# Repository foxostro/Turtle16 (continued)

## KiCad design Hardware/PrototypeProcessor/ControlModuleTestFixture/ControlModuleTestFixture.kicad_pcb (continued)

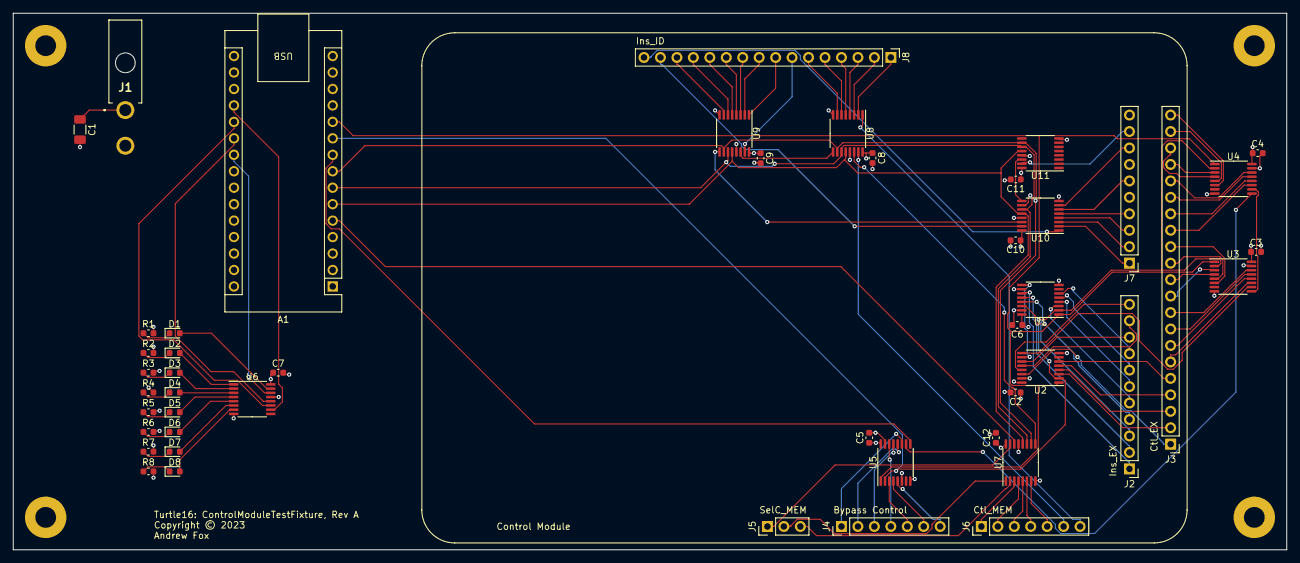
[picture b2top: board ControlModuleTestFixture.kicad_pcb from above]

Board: 4 copper layers, 196.5 x 82.8 mm, 52 parts (0 on the bottom side), 109 nets.

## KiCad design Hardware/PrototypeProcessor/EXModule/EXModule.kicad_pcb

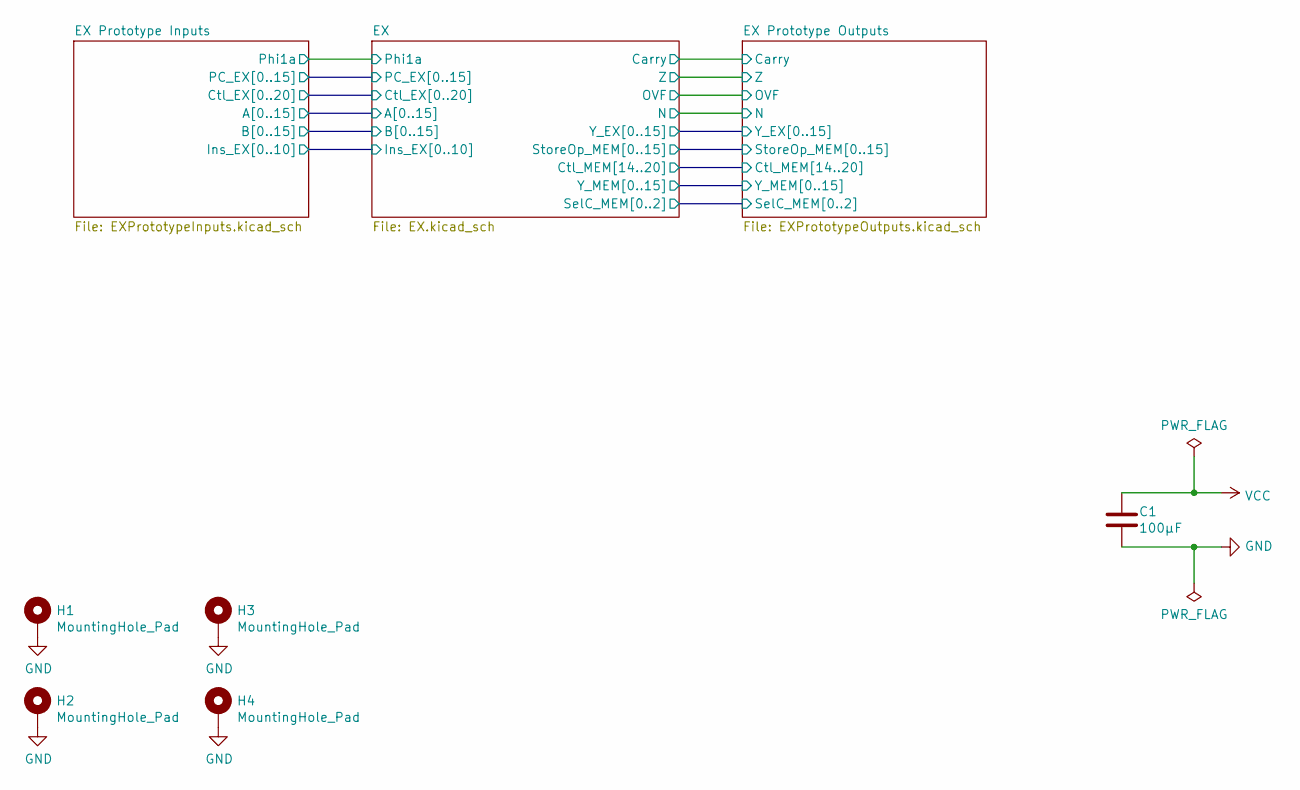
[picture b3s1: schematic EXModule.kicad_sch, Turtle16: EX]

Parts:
C1: 100µF; C_1206_3216Metric_Pad1.33x1.80mm_HandSolder
H1, H2, H3, H4: MountingHole_Pad; MountingHole_3.2mm_M3_Pad

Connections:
GND: C1.2, H1.1, H2.1, H3.1, H4.1; also elsewhere on the board
VCC: C1.1; also elsewhere on the board

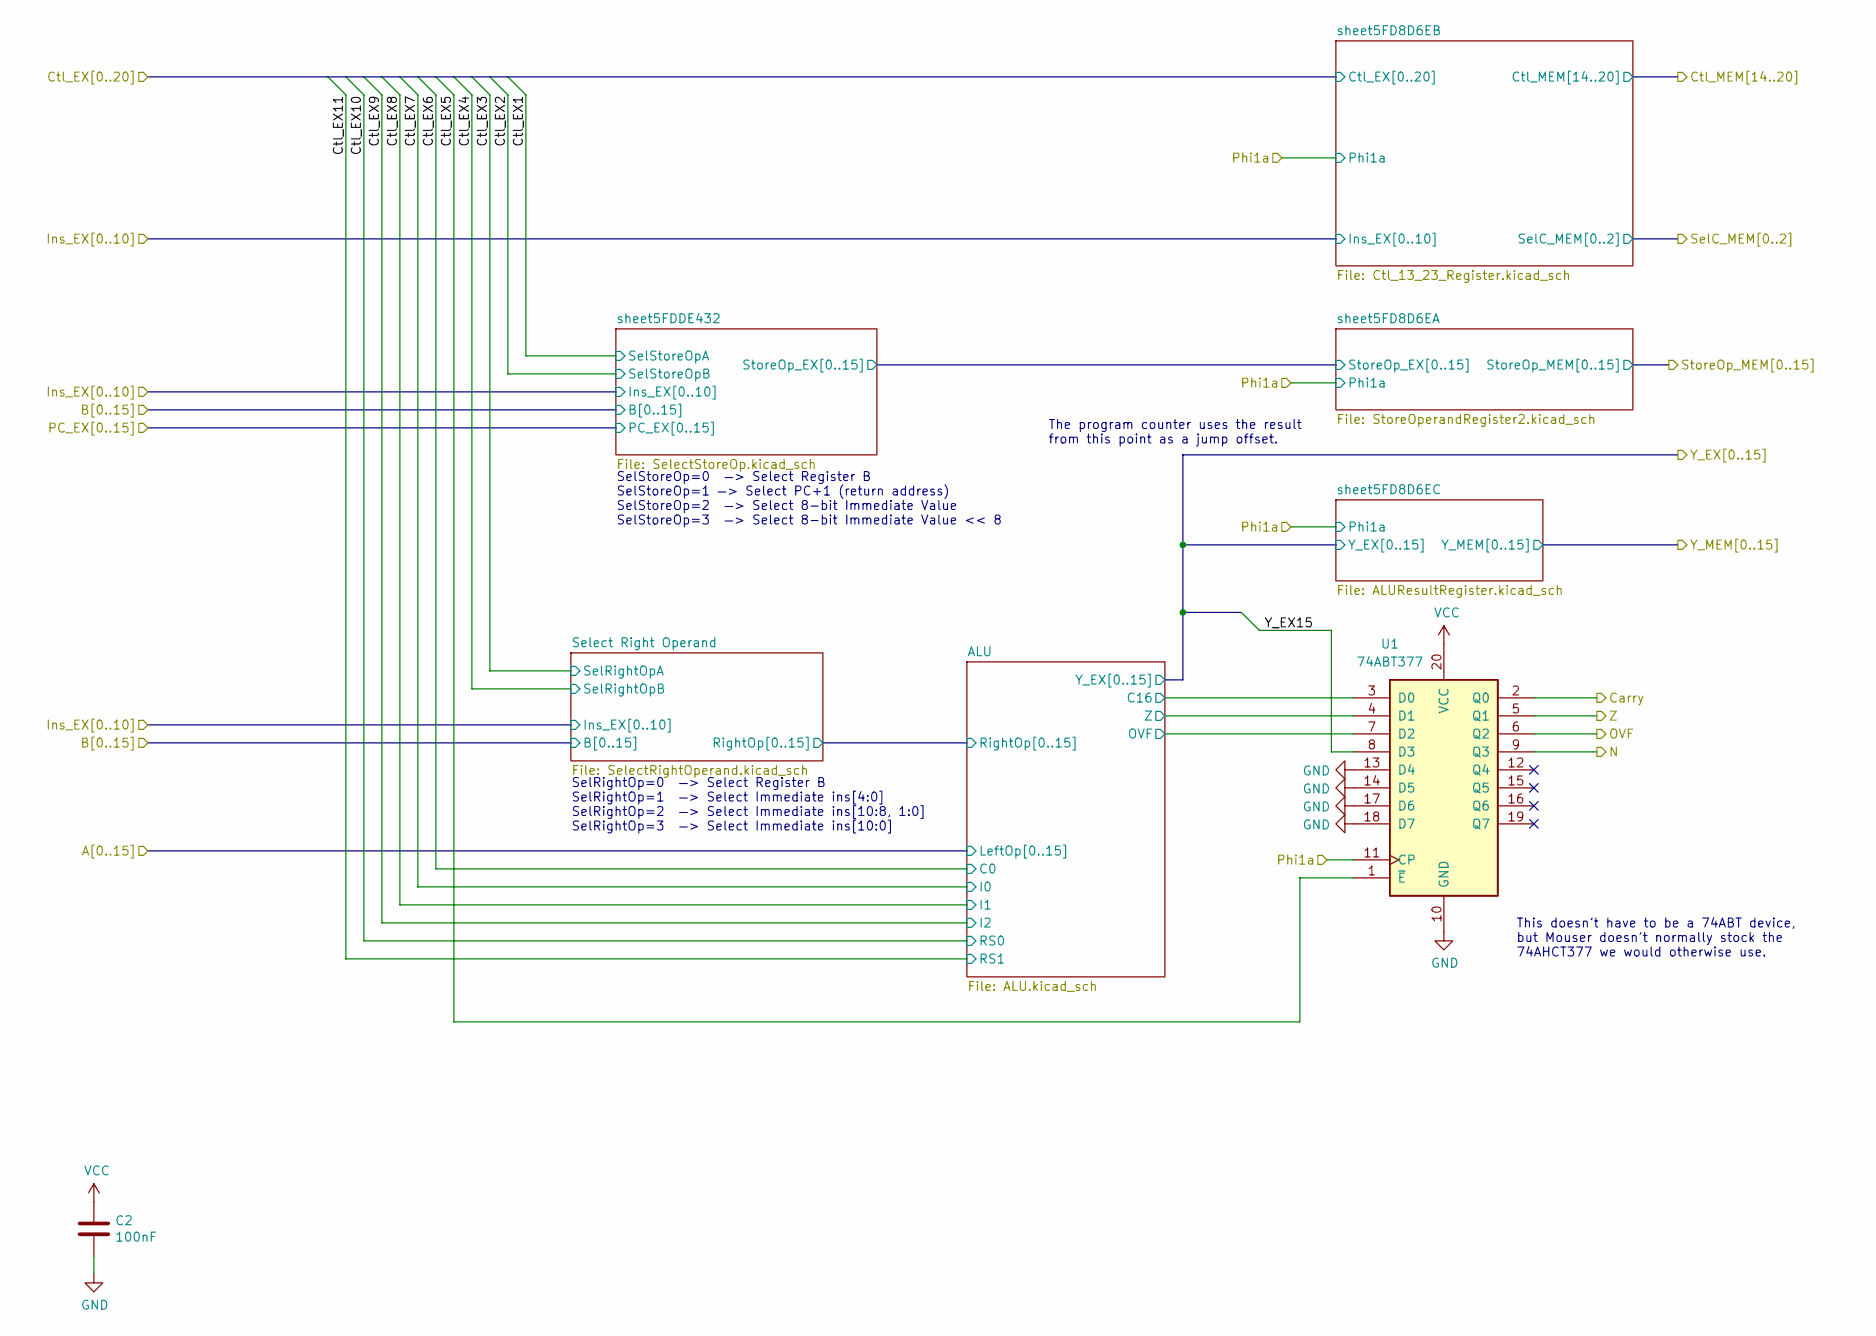
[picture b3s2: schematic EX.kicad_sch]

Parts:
C2: 100nF; C_0603_1608Metric_Pad1.08x0.95mm_HandSolder
U1: 74ABT377; TSSOP-20_4.4x6.5mm_P0.65mm

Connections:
/EX Prototype Inputs/Ctl_EX5: U1.1 (~E); also elsewhere on the board
/EX Prototype Inputs/Phi1a: U1.11 (CP); also elsewhere on the board
/EX Prototype Outputs/Carry: U1.2 (Q0); also elsewhere on the board
/EX Prototype Outputs/N: U1.9 (Q3); also elsewhere on the board
/EX Prototype Outputs/OVF: U1.6 (Q2); also elsewhere on the board
/EX Prototype Outputs/Y_EX15: U1.8 (D3); also elsewhere on the board
/EX Prototype Outputs/Z: U1.5 (Q1); also elsewhere on the board
/EX/ALU/C16: U1.3 (D0); also elsewhere on the board
/EX/ALU/OVF: U1.7 (D2); also elsewhere on the board
/EX/ALU/Z: U1.4 (D1); also elsewhere on the board
GND: C2.2, U1.10 (GND), U1.13 (D4), U1.14 (D5), U1.17 (D6), U1.18 (D7); also elsewhere on the board
VCC: C2.1, U1.20 (VCC); also elsewhere on the board

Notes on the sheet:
SelStoreOp=0 —> Select Register B SelStoreOp=1 —> Select PC+1 (return address) SelStoreOp=2 —> Select 8-bit Immediate Value SelStoreOp=3 —> Select 8-bit Immediate Value << 8
This doesn’t have to be a 74ABT device, but Mouser doesn’t normally stock the 74AHCT377 we would otherwise use.
SelRightOp=0 —> Select Register B SelRightOp=1 —> Select Immediate ins[4:0] SelRightOp=2 —> Select Immediate ins[10:8, 1:0] SelRightOp=3 —> Select Immediate ins[10:0]
The program counter uses the result from this point as a jump offset.

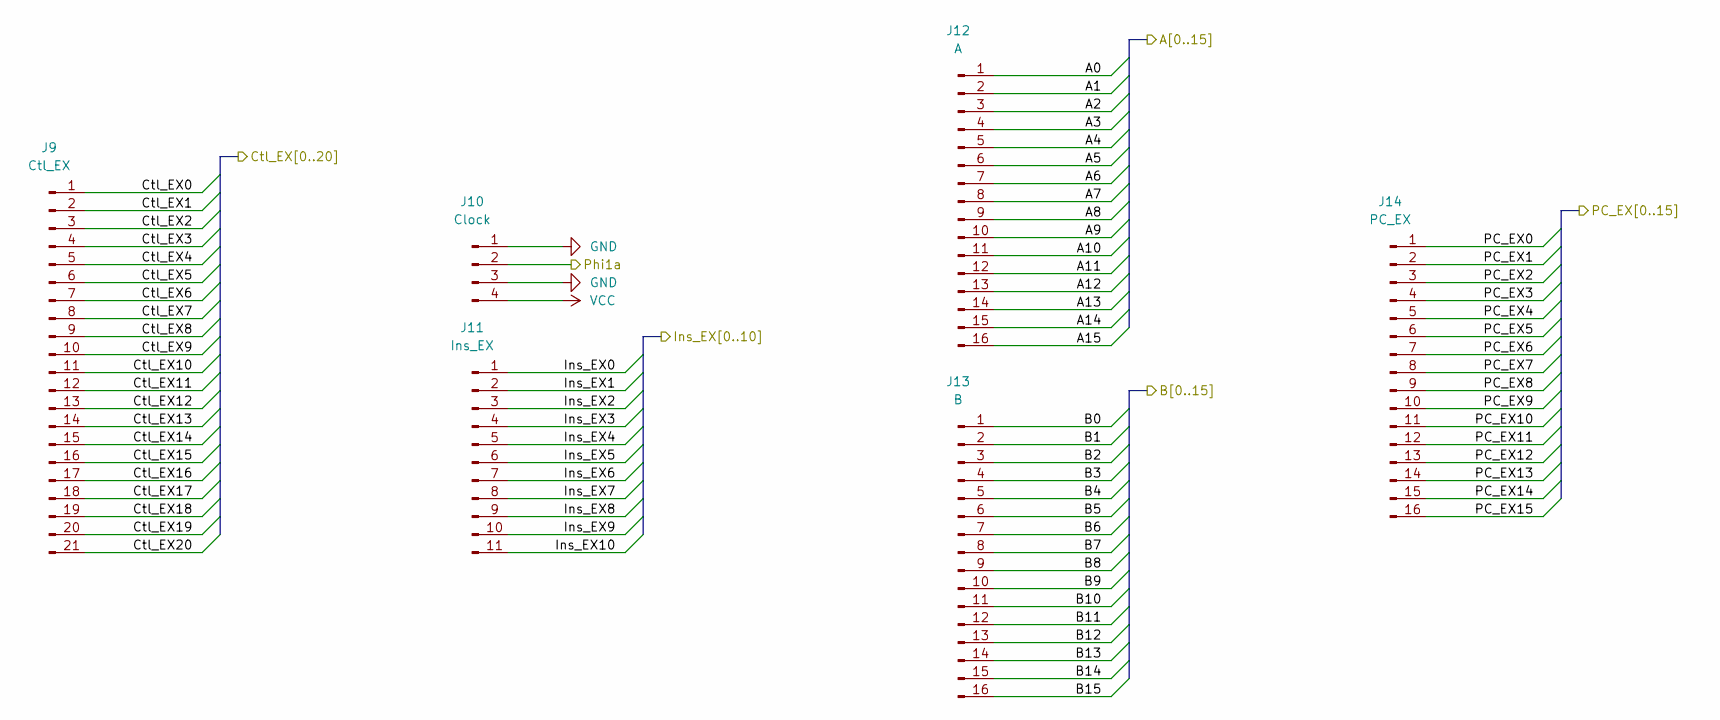
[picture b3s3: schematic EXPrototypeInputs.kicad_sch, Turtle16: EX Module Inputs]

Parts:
J9: Ctl_EX; PinHeader_1x21_P2.54mm_Vertical
J10: Clock; PinHeader_1x04_P2.54mm_Vertical
J11: Ins_EX; PinHeader_1x11_P2.54mm_Vertical
J12: A; PinHeader_1x16_P2.54mm_Vertical
J13: B; PinHeader_1x16_P2.54mm_Vertical
J14: PC_EX; PinHeader_1x16_P2.54mm_Vertical

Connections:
/EX Prototype Inputs/A0: J12.1; also elsewhere on the board
/EX Prototype Inputs/A1: J12.2; also elsewhere on the board
/EX Prototype Inputs/A2: J12.3; also elsewhere on the board
/EX Prototype Inputs/A3: J12.4; also elsewhere on the board
/EX Prototype Inputs/A4: J12.5; also elsewhere on the board
/EX Prototype Inputs/A5: J12.6; also elsewhere on the board
/EX Prototype Inputs/A6: J12.7; also elsewhere on the board
/EX Prototype Inputs/A7: J12.8; also elsewhere on the board
/EX Prototype Inputs/A8: J12.9; also elsewhere on the board
/EX Prototype Inputs/A9: J12.10; also elsewhere on the board
/EX Prototype Inputs/A10: J12.11; also elsewhere on the board
/EX Prototype Inputs/A11: J12.12; also elsewhere on the board
/EX Prototype Inputs/A12: J12.13; also elsewhere on the board
/EX Prototype Inputs/A13: J12.14; also elsewhere on the board
/EX Prototype Inputs/A14: J12.15; also elsewhere on the board
/EX Prototype Inputs/A15: J12.16; also elsewhere on the board
/EX Prototype Inputs/B0: J13.1; also elsewhere on the board
/EX Prototype Inputs/B1: J13.2; also elsewhere on the board
/EX Prototype Inputs/B2: J13.3; also elsewhere on the board
/EX Prototype Inputs/B3: J13.4; also elsewhere on the board
/EX Prototype Inputs/B4: J13.5; also elsewhere on the board
/EX Prototype Inputs/B5: J13.6; also elsewhere on the board
/EX Prototype Inputs/B6: J13.7; also elsewhere on the board
/EX Prototype Inputs/B7: J13.8; also elsewhere on the board
/EX Prototype Inputs/B8: J13.9; also elsewhere on the board
/EX Prototype Inputs/B9: J13.10; also elsewhere on the board
/EX Prototype Inputs/B10: J13.11; also elsewhere on the board
/EX Prototype Inputs/B11: J13.12; also elsewhere on the board
/EX Prototype Inputs/B12: J13.13; also elsewhere on the board
/EX Prototype Inputs/B13: J13.14; also elsewhere on the board
/EX Prototype Inputs/B14: J13.15; also elsewhere on the board
/EX Prototype Inputs/B15: J13.16; also elsewhere on the board
/EX Prototype Inputs/Ctl_EX0: J9.1
/EX Prototype Inputs/Ctl_EX1: J9.2; also elsewhere on the board
/EX Prototype Inputs/Ctl_EX2: J9.3; also elsewhere on the board
/EX Prototype Inputs/Ctl_EX3: J9.4; also elsewhere on the board
/EX Prototype Inputs/Ctl_EX4: J9.5; also elsewhere on the board
/EX Prototype Inputs/Ctl_EX5: J9.6; also elsewhere on the board
/EX Prototype Inputs/Ctl_EX6: J9.7; also elsewhere on the board
/EX Prototype Inputs/Ctl_EX7: J9.8; also elsewhere on the board
/EX Prototype Inputs/Ctl_EX8: J9.9; also elsewhere on the board
/EX Prototype Inputs/Ctl_EX9: J9.10; also elsewhere on the board
/EX Prototype Inputs/Ctl_EX10: J9.11; also elsewhere on the board
/EX Prototype Inputs/Ctl_EX11: J9.12; also elsewhere on the board
/EX Prototype Inputs/Ctl_EX12: J9.13
/EX Prototype Inputs/Ctl_EX13: J9.14
/EX Prototype Inputs/Ctl_EX14: J9.15; also elsewhere on the board
/EX Prototype Inputs/Ctl_EX15: J9.16; also elsewhere on the board
/EX Prototype Inputs/Ctl_EX16: J9.17; also elsewhere on the board
/EX Prototype Inputs/Ctl_EX17: J9.18; also elsewhere on the board
/EX Prototype Inputs/Ctl_EX18: J9.19; also elsewhere on the board
/EX Prototype Inputs/Ctl_EX19: J9.20; also elsewhere on the board
/EX Prototype Inputs/Ctl_EX20: J9.21; also elsewhere on the board
/EX Prototype Inputs/Ins_EX0: J11.1; also elsewhere on the board
/EX Prototype Inputs/Ins_EX1: J11.2; also elsewhere on the board
/EX Prototype Inputs/Ins_EX2: J11.3; also elsewhere on the board
/EX Prototype Inputs/Ins_EX3: J11.4; also elsewhere on the board
/EX Prototype Inputs/Ins_EX4: J11.5; also elsewhere on the board
/EX Prototype Inputs/Ins_EX5: J11.6; also elsewhere on the board
/EX Prototype Inputs/Ins_EX6: J11.7; also elsewhere on the board
/EX Prototype Inputs/Ins_EX7: J11.8; also elsewhere on the board
/EX Prototype Inputs/Ins_EX8: J11.9; also elsewhere on the board
/EX Prototype Inputs/Ins_EX9: J11.10; also elsewhere on the board
/EX Prototype Inputs/Ins_EX10: J11.11; also elsewhere on the board
/EX Prototype Inputs/PC_EX0: J14.1; also elsewhere on the board
/EX Prototype Inputs/PC_EX1: J14.2; also elsewhere on the board
/EX Prototype Inputs/PC_EX2: J14.3; also elsewhere on the board
/EX Prototype Inputs/PC_EX3: J14.4; also elsewhere on the board
/EX Prototype Inputs/PC_EX4: J14.5; also elsewhere on the board
/EX Prototype Inputs/PC_EX5: J14.6; also elsewhere on the board
/EX Prototype Inputs/PC_EX6: J14.7; also elsewhere on the board
/EX Prototype Inputs/PC_EX7: J14.8; also elsewhere on the board
/EX Prototype Inputs/PC_EX8: J14.9; also elsewhere on the board
/EX Prototype Inputs/PC_EX9: J14.10; also elsewhere on the board
/EX Prototype Inputs/PC_EX10: J14.11; also elsewhere on the board
/EX Prototype Inputs/PC_EX11: J14.12; also elsewhere on the board
/EX Prototype Inputs/PC_EX12: J14.13; also elsewhere on the board
/EX Prototype Inputs/PC_EX13: J14.14; also elsewhere on the board
/EX Prototype Inputs/PC_EX14: J14.15; also elsewhere on the board
/EX Prototype Inputs/PC_EX15: J14.16; also elsewhere on the board
/EX Prototype Inputs/Phi1a: J10.2; also elsewhere on the board
GND: J10.1, J10.3; also elsewhere on the board
VCC: J10.4; also elsewhere on the board

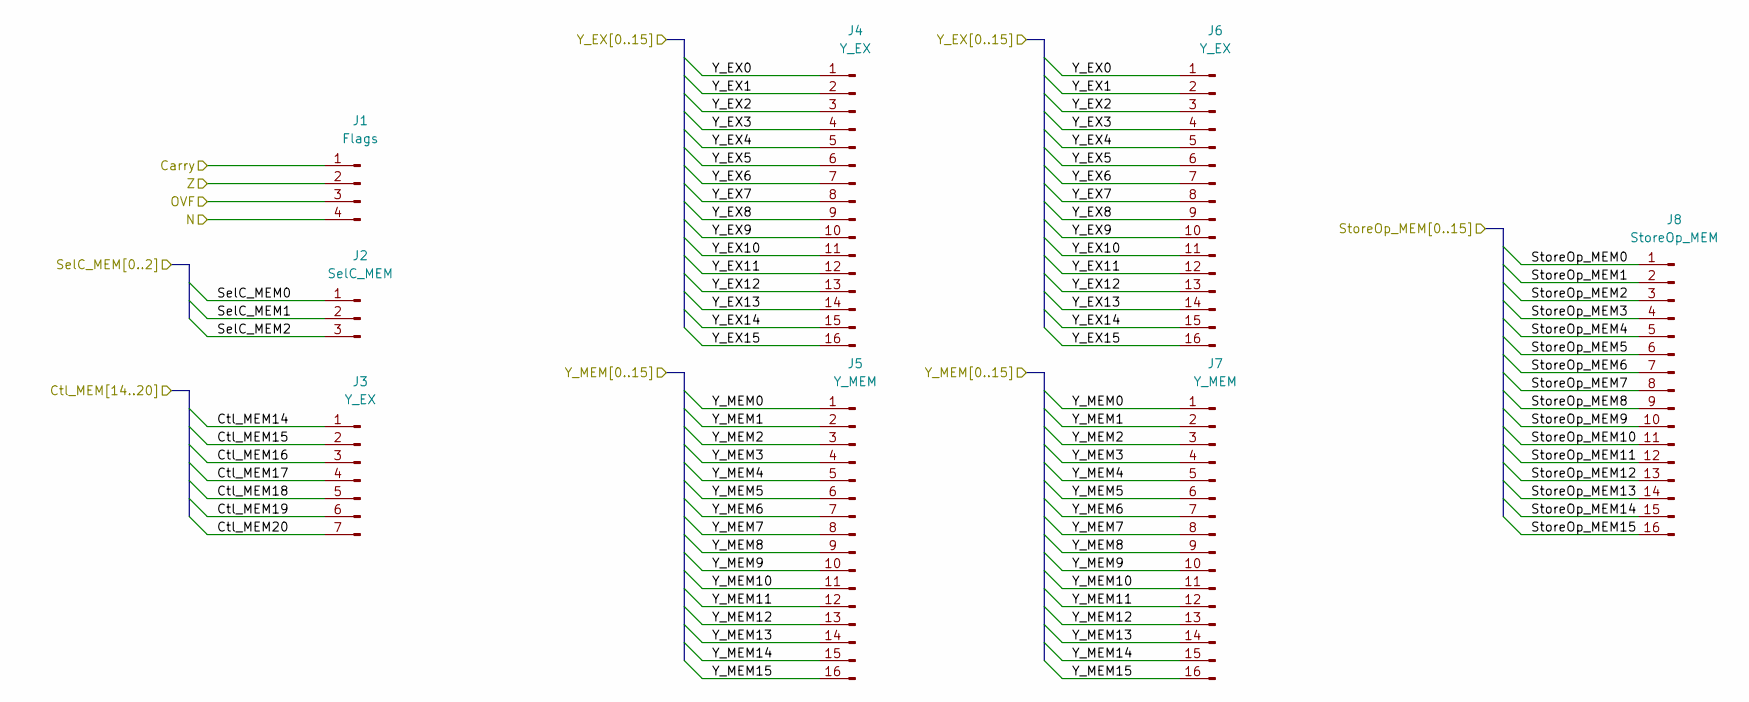
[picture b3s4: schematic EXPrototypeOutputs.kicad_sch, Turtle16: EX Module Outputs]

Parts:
J1: Flags; PinHeader_1x04_P2.54mm_Vertical
J2: SelC_MEM; PinHeader_1x03_P2.54mm_Vertical
J3: Y_EX; PinHeader_1x07_P2.54mm_Vertical
J4, J6: Y_EX; PinHeader_1x16_P2.54mm_Vertical
J5, J7: Y_MEM; PinHeader_1x16_P2.54mm_Vertical
J8: StoreOp_MEM; PinHeader_1x16_P2.54mm_Vertical

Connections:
/EX Prototype Outputs/Carry: J1.1; also elsewhere on the board
/EX Prototype Outputs/Ctl_MEM14: J3.1; also elsewhere on the board
/EX Prototype Outputs/Ctl_MEM15: J3.2; also elsewhere on the board
/EX Prototype Outputs/Ctl_MEM16: J3.3; also elsewhere on the board
/EX Prototype Outputs/Ctl_MEM17: J3.4; also elsewhere on the board
/EX Prototype Outputs/Ctl_MEM18: J3.5; also elsewhere on the board
/EX Prototype Outputs/Ctl_MEM19: J3.6; also elsewhere on the board
/EX Prototype Outputs/Ctl_MEM20: J3.7; also elsewhere on the board
/EX Prototype Outputs/N: J1.4; also elsewhere on the board
/EX Prototype Outputs/OVF: J1.3; also elsewhere on the board
/EX Prototype Outputs/SelC_MEM0: J2.1; also elsewhere on the board
/EX Prototype Outputs/SelC_MEM1: J2.2; also elsewhere on the board
/EX Prototype Outputs/SelC_MEM2: J2.3; also elsewhere on the board
/EX Prototype Outputs/StoreOp_MEM0: J8.1; also elsewhere on the board
/EX Prototype Outputs/StoreOp_MEM1: J8.2; also elsewhere on the board
/EX Prototype Outputs/StoreOp_MEM2: J8.3; also elsewhere on the board
/EX Prototype Outputs/StoreOp_MEM3: J8.4; also elsewhere on the board
/EX Prototype Outputs/StoreOp_MEM4: J8.5; also elsewhere on the board
/EX Prototype Outputs/StoreOp_MEM5: J8.6; also elsewhere on the board
/EX Prototype Outputs/StoreOp_MEM6: J8.7; also elsewhere on the board
/EX Prototype Outputs/StoreOp_MEM7: J8.8; also elsewhere on the board
/EX Prototype Outputs/StoreOp_MEM8: J8.9; also elsewhere on the board
/EX Prototype Outputs/StoreOp_MEM9: J8.10; also elsewhere on the board
/EX Prototype Outputs/StoreOp_MEM10: J8.11; also elsewhere on the board
/EX Prototype Outputs/StoreOp_MEM11: J8.12; also elsewhere on the board
/EX Prototype Outputs/StoreOp_MEM12: J8.13; also elsewhere on the board
/EX Prototype Outputs/StoreOp_MEM13: J8.14; also elsewhere on the board
/EX Prototype Outputs/StoreOp_MEM14: J8.15; also elsewhere on the board
/EX Prototype Outputs/StoreOp_MEM15: J8.16; also elsewhere on the board
/EX Prototype Outputs/Y_EX0: J4.1, J6.1; also elsewhere on the board
/EX Prototype Outputs/Y_EX1: J4.2, J6.2; also elsewhere on the board
/EX Prototype Outputs/Y_EX2: J4.3, J6.3; also elsewhere on the board
/EX Prototype Outputs/Y_EX3: J4.4, J6.4; also elsewhere on the board
/EX Prototype Outputs/Y_EX4: J4.5, J6.5; also elsewhere on the board
/EX Prototype Outputs/Y_EX5: J4.6, J6.6; also elsewhere on the board
/EX Prototype Outputs/Y_EX6: J4.7, J6.7; also elsewhere on the board
/EX Prototype Outputs/Y_EX7: J4.8, J6.8; also elsewhere on the board
/EX Prototype Outputs/Y_EX8: J4.9, J6.9; also elsewhere on the board
/EX Prototype Outputs/Y_EX9: J4.10, J6.10; also elsewhere on the board
/EX Prototype Outputs/Y_EX10: J4.11, J6.11; also elsewhere on the board
/EX Prototype Outputs/Y_EX11: J4.12, J6.12; also elsewhere on the board
/EX Prototype Outputs/Y_EX12: J4.13, J6.13; also elsewhere on the board
/EX Prototype Outputs/Y_EX13: J4.14, J6.14; also elsewhere on the board
/EX Prototype Outputs/Y_EX14: J4.15, J6.15; also elsewhere on the board
/EX Prototype Outputs/Y_EX15: J4.16, J6.16; also elsewhere on the board
/EX Prototype Outputs/Y_MEM0: J5.1, J7.1; also elsewhere on the board
/EX Prototype Outputs/Y_MEM1: J5.2, J7.2; also elsewhere on the board
/EX Prototype Outputs/Y_MEM2: J5.3, J7.3; also elsewhere on the board
/EX Prototype Outputs/Y_MEM3: J5.4, J7.4; also elsewhere on the board
/EX Prototype Outputs/Y_MEM4: J5.5, J7.5; also elsewhere on the board
/EX Prototype Outputs/Y_MEM5: J5.6, J7.6; also elsewhere on the board
/EX Prototype Outputs/Y_MEM6: J5.7, J7.7; also elsewhere on the board
/EX Prototype Outputs/Y_MEM7: J5.8, J7.8; also elsewhere on the board
/EX Prototype Outputs/Y_MEM8: J5.9, J7.9; also elsewhere on the board
/EX Prototype Outputs/Y_MEM9: J5.10, J7.10; also elsewhere on the board
/EX Prototype Outputs/Y_MEM10: J5.11, J7.11; also elsewhere on the board
/EX Prototype Outputs/Y_MEM11: J5.12, J7.12; also elsewhere on the board
/EX Prototype Outputs/Y_MEM12: J5.13, J7.13; also elsewhere on the board
/EX Prototype Outputs/Y_MEM13: J5.14, J7.14; also elsewhere on the board
/EX Prototype Outputs/Y_MEM14: J5.15, J7.15; also elsewhere on the board
/EX Prototype Outputs/Y_MEM15: J5.16, J7.16; also elsewhere on the board
/EX Prototype Outputs/Z: J1.2; also elsewhere on the board

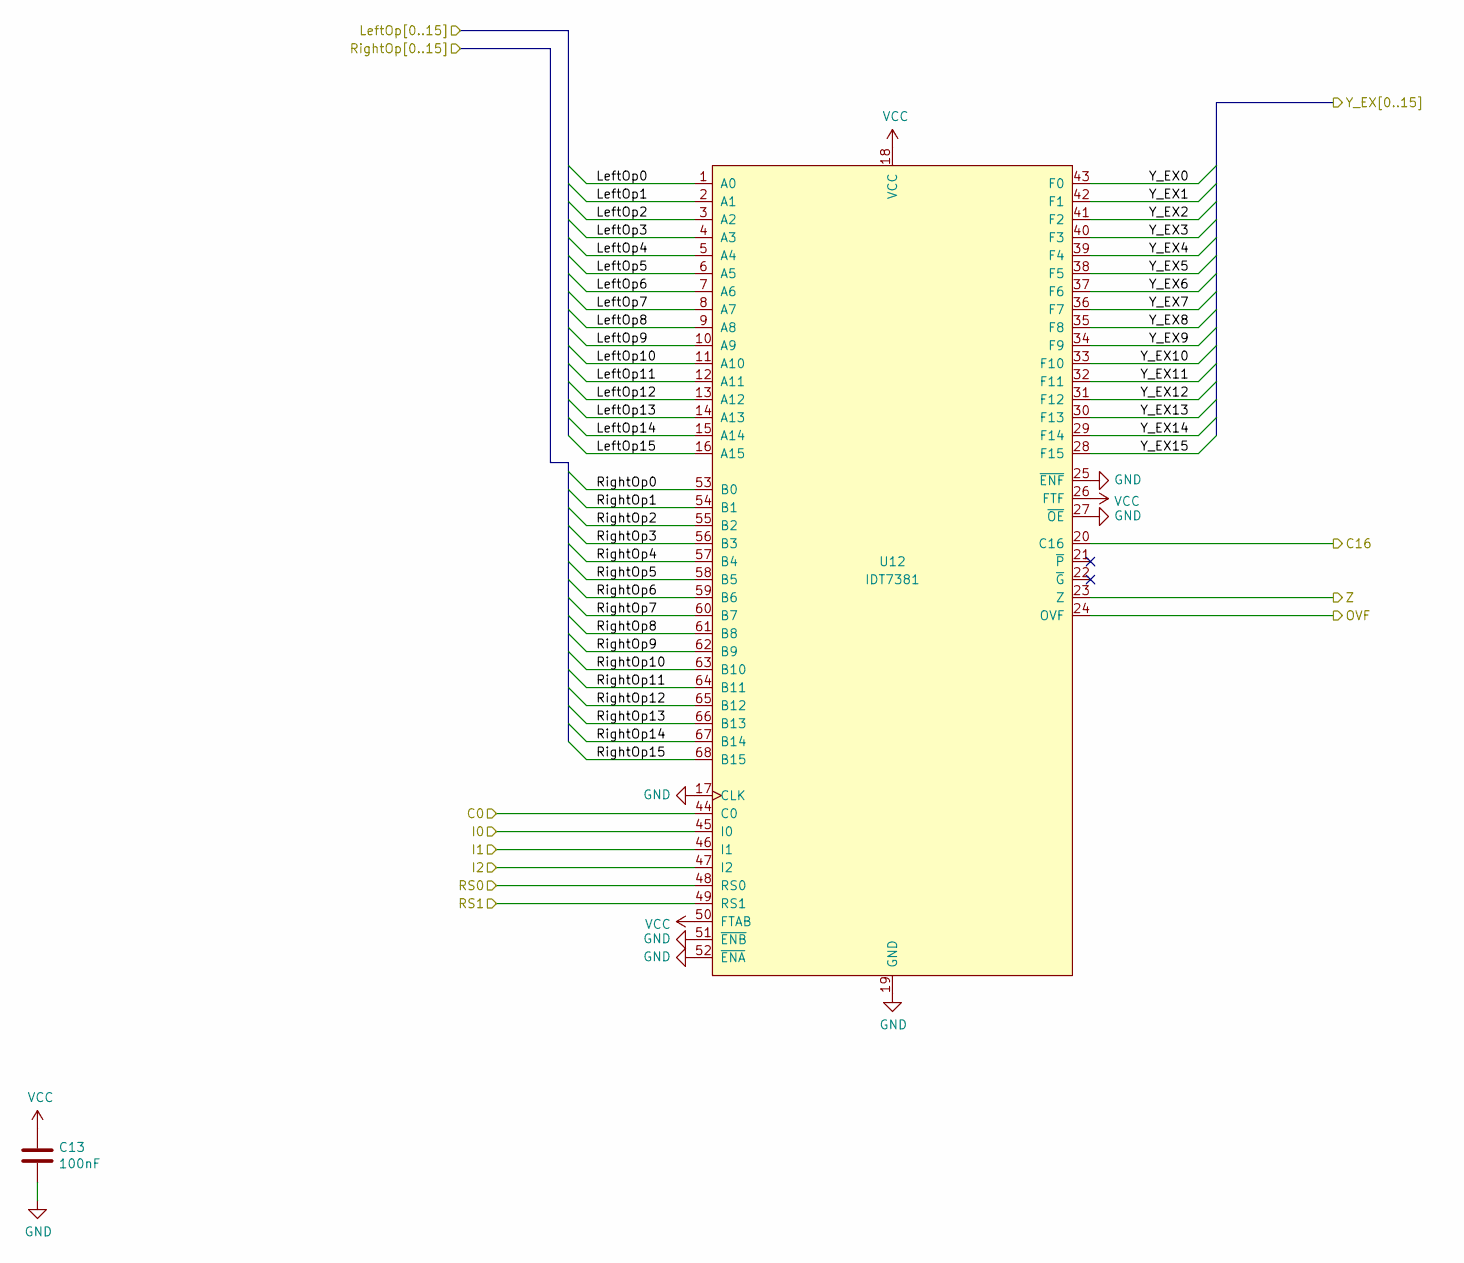
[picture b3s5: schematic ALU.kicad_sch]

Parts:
C13: 100nF; C_0603_1608Metric_Pad1.08x0.95mm_HandSolder
U12: IDT7381; PLCC-68_SMD-Socket

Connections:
/EX Prototype Inputs/A0: U12.1 (A0); also elsewhere on the board
/EX Prototype Inputs/A1: U12.2 (A1); also elsewhere on the board
/EX Prototype Inputs/A2: U12.3 (A2); also elsewhere on the board
/EX Prototype Inputs/A3: U12.4 (A3); also elsewhere on the board
/EX Prototype Inputs/A4: U12.5 (A4); also elsewhere on the board
/EX Prototype Inputs/A5: U12.6 (A5); also elsewhere on the board
/EX Prototype Inputs/A6: U12.7 (A6); also elsewhere on the board
/EX Prototype Inputs/A7: U12.8 (A7); also elsewhere on the board
/EX Prototype Inputs/A8: U12.9 (A8); also elsewhere on the board
/EX Prototype Inputs/A9: U12.10 (A9); also elsewhere on the board
/EX Prototype Inputs/A10: U12.11 (A10); also elsewhere on the board
/EX Prototype Inputs/A11: U12.12 (A11); also elsewhere on the board
/EX Prototype Inputs/A12: U12.13 (A12); also elsewhere on the board
/EX Prototype Inputs/A13: U12.14 (A13); also elsewhere on the board
/EX Prototype Inputs/A14: U12.15 (A14); also elsewhere on the board
/EX Prototype Inputs/A15: U12.16 (A15); also elsewhere on the board
/EX Prototype Inputs/Ctl_EX6: U12.44 (C0); also elsewhere on the board
/EX Prototype Inputs/Ctl_EX7: U12.45 (I0); also elsewhere on the board
/EX Prototype Inputs/Ctl_EX8: U12.46 (I1); also elsewhere on the board
/EX Prototype Inputs/Ctl_EX9: U12.47 (I2); also elsewhere on the board
/EX Prototype Inputs/Ctl_EX10: U12.48 (RS0); also elsewhere on the board
/EX Prototype Inputs/Ctl_EX11: U12.49 (RS1); also elsewhere on the board
/EX Prototype Outputs/Y_EX0: U12.43 (F0); also elsewhere on the board
/EX Prototype Outputs/Y_EX1: U12.42 (F1); also elsewhere on the board
/EX Prototype Outputs/Y_EX2: U12.41 (F2); also elsewhere on the board
/EX Prototype Outputs/Y_EX3: U12.40 (F3); also elsewhere on the board
/EX Prototype Outputs/Y_EX4: U12.39 (F4); also elsewhere on the board
/EX Prototype Outputs/Y_EX5: U12.38 (F5); also elsewhere on the board
/EX Prototype Outputs/Y_EX6: U12.37 (F6); also elsewhere on the board
/EX Prototype Outputs/Y_EX7: U12.36 (F7); also elsewhere on the board
/EX Prototype Outputs/Y_EX8: U12.35 (F8); also elsewhere on the board
/EX Prototype Outputs/Y_EX9: U12.34 (F9); also elsewhere on the board
/EX Prototype Outputs/Y_EX10: U12.33 (F10); also elsewhere on the board
/EX Prototype Outputs/Y_EX11: U12.32 (F11); also elsewhere on the board
/EX Prototype Outputs/Y_EX12: U12.31 (F12); also elsewhere on the board
/EX Prototype Outputs/Y_EX13: U12.30 (F13); also elsewhere on the board
/EX Prototype Outputs/Y_EX14: U12.29 (F14); also elsewhere on the board
/EX Prototype Outputs/Y_EX15: U12.28 (F15); also elsewhere on the board
/EX/ALU/C16: U12.20 (C16); also elsewhere on the board
/EX/ALU/OVF: U12.24 (OVF); also elsewhere on the board
/EX/ALU/RightOp0: U12.53 (B0); also elsewhere on the board
/EX/ALU/RightOp1: U12.54 (B1); also elsewhere on the board
/EX/ALU/RightOp2: U12.55 (B2); also elsewhere on the board
/EX/ALU/RightOp3: U12.56 (B3); also elsewhere on the board
/EX/ALU/RightOp4: U12.57 (B4); also elsewhere on the board
/EX/ALU/RightOp5: U12.58 (B5); also elsewhere on the board
/EX/ALU/RightOp6: U12.59 (B6); also elsewhere on the board
/EX/ALU/RightOp7: U12.60 (B7); also elsewhere on the board
/EX/ALU/RightOp8: U12.61 (B8); also elsewhere on the board
/EX/ALU/RightOp9: U12.62 (B9); also elsewhere on the board
/EX/ALU/RightOp10: U12.63 (B10); also elsewhere on the board
/EX/ALU/RightOp11: U12.64 (B11); also elsewhere on the board
/EX/ALU/RightOp12: U12.65 (B12); also elsewhere on the board
/EX/ALU/RightOp13: U12.66 (B13); also elsewhere on the board
/EX/ALU/RightOp14: U12.67 (B14); also elsewhere on the board
/EX/ALU/RightOp15: U12.68 (B15); also elsewhere on the board
/EX/ALU/Z: U12.23 (Z); also elsewhere on the board
GND: C13.2, U12.17 (CLK), U12.19 (GND), U12.25 (~ENF), U12.27 (~OE), U12.51 (~ENB), U12.52 (~ENA); also elsewhere on the board
VCC: C13.1, U12.18 (VCC), U12.26 (FTF), U12.50 (FTAB); also elsewhere on the board

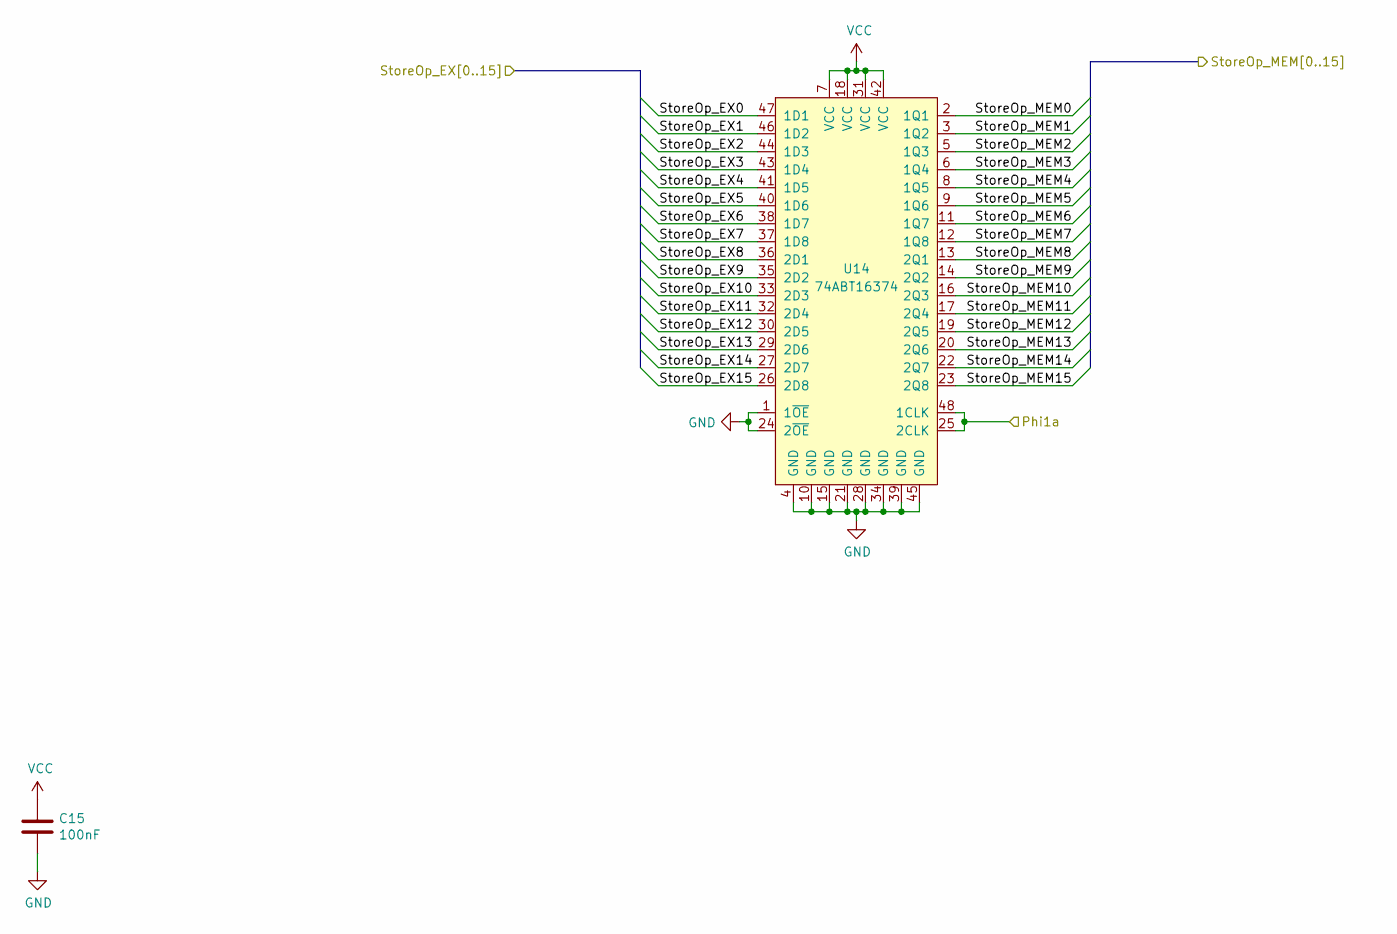
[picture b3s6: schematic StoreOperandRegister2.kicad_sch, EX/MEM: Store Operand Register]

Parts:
C15: 100nF; C_0603_1608Metric_Pad1.08x0.95mm_HandSolder
U14: 74ABT16374; TSSOP-48_6.1x12.5mm_P0.5mm

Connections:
/EX Prototype Inputs/Phi1a: U14.25 (2CLK), U14.48 (1CLK); also elsewhere on the board
/EX Prototype Outputs/StoreOp_MEM0: U14.2 (1Q1); also elsewhere on the board
/EX Prototype Outputs/StoreOp_MEM1: U14.3 (1Q2); also elsewhere on the board
/EX Prototype Outputs/StoreOp_MEM2: U14.5 (1Q3); also elsewhere on the board
/EX Prototype Outputs/StoreOp_MEM3: U14.6 (1Q4); also elsewhere on the board
/EX Prototype Outputs/StoreOp_MEM4: U14.8 (1Q5); also elsewhere on the board
/EX Prototype Outputs/StoreOp_MEM5: U14.9 (1Q6); also elsewhere on the board
/EX Prototype Outputs/StoreOp_MEM6: U14.11 (1Q7); also elsewhere on the board
/EX Prototype Outputs/StoreOp_MEM7: U14.12 (1Q8); also elsewhere on the board
/EX Prototype Outputs/StoreOp_MEM8: U14.13 (2Q1); also elsewhere on the board
/EX Prototype Outputs/StoreOp_MEM9: U14.14 (2Q2); also elsewhere on the board
/EX Prototype Outputs/StoreOp_MEM10: U14.16 (2Q3); also elsewhere on the board
/EX Prototype Outputs/StoreOp_MEM11: U14.17 (2Q4); also elsewhere on the board
/EX Prototype Outputs/StoreOp_MEM12: U14.19 (2Q5); also elsewhere on the board
/EX Prototype Outputs/StoreOp_MEM13: U14.20 (2Q6); also elsewhere on the board
/EX Prototype Outputs/StoreOp_MEM14: U14.22 (2Q7); also elsewhere on the board
/EX Prototype Outputs/StoreOp_MEM15: U14.23 (2Q8); also elsewhere on the board
/EX/sheet5FD8D6EA/StoreOp_EX0: U14.47 (1D1); also elsewhere on the board
/EX/sheet5FD8D6EA/StoreOp_EX1: U14.46 (1D2); also elsewhere on the board
/EX/sheet5FD8D6EA/StoreOp_EX2: U14.44 (1D3); also elsewhere on the board
/EX/sheet5FD8D6EA/StoreOp_EX3: U14.43 (1D4); also elsewhere on the board
/EX/sheet5FD8D6EA/StoreOp_EX4: U14.41 (1D5); also elsewhere on the board
/EX/sheet5FD8D6EA/StoreOp_EX5: U14.40 (1D6); also elsewhere on the board
/EX/sheet5FD8D6EA/StoreOp_EX6: U14.38 (1D7); also elsewhere on the board
/EX/sheet5FD8D6EA/StoreOp_EX7: U14.37 (1D8); also elsewhere on the board
/EX/sheet5FD8D6EA/StoreOp_EX8: U14.36 (2D1); also elsewhere on the board
/EX/sheet5FD8D6EA/StoreOp_EX9: U14.35 (2D2); also elsewhere on the board
/EX/sheet5FD8D6EA/StoreOp_EX10: U14.33 (2D3); also elsewhere on the board
/EX/sheet5FD8D6EA/StoreOp_EX11: U14.32 (2D4); also elsewhere on the board
/EX/sheet5FD8D6EA/StoreOp_EX12: U14.30 (2D5); also elsewhere on the board
/EX/sheet5FD8D6EA/StoreOp_EX13: U14.29 (2D6); also elsewhere on the board
/EX/sheet5FD8D6EA/StoreOp_EX14: U14.27 (2D7); also elsewhere on the board
/EX/sheet5FD8D6EA/StoreOp_EX15: U14.26 (2D8); also elsewhere on the board
GND: C15.2, U14.1 (1~OE), U14.4 (GND), U14.10 (GND), U14.15 (GND), U14.21 (GND), U14.24 (2~OE), U14.28 (GND), U14.34 (GND), U14.39 (GND), U14.45 (GND); also elsewhere on the board
VCC: C15.1, U14.7 (VCC), U14.18 (VCC), U14.31 (VCC), U14.42 (VCC); also elsewhere on the board
